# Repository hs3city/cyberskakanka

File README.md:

# cyberskakanka

## Wiring the Stuff Together

### Connecting Arduino and Weight Sensors

### Connecting Arduino and Raspberry Pi via I2C

### Connecting Raspberry Pi with WS212B LED Strip

## The Hardware

### The Base

### The Base with Two Tiles Fit

### The Tile

- 16mm MDF on the bottom
- a layer of white cardboard
- 5mm transparent plexi

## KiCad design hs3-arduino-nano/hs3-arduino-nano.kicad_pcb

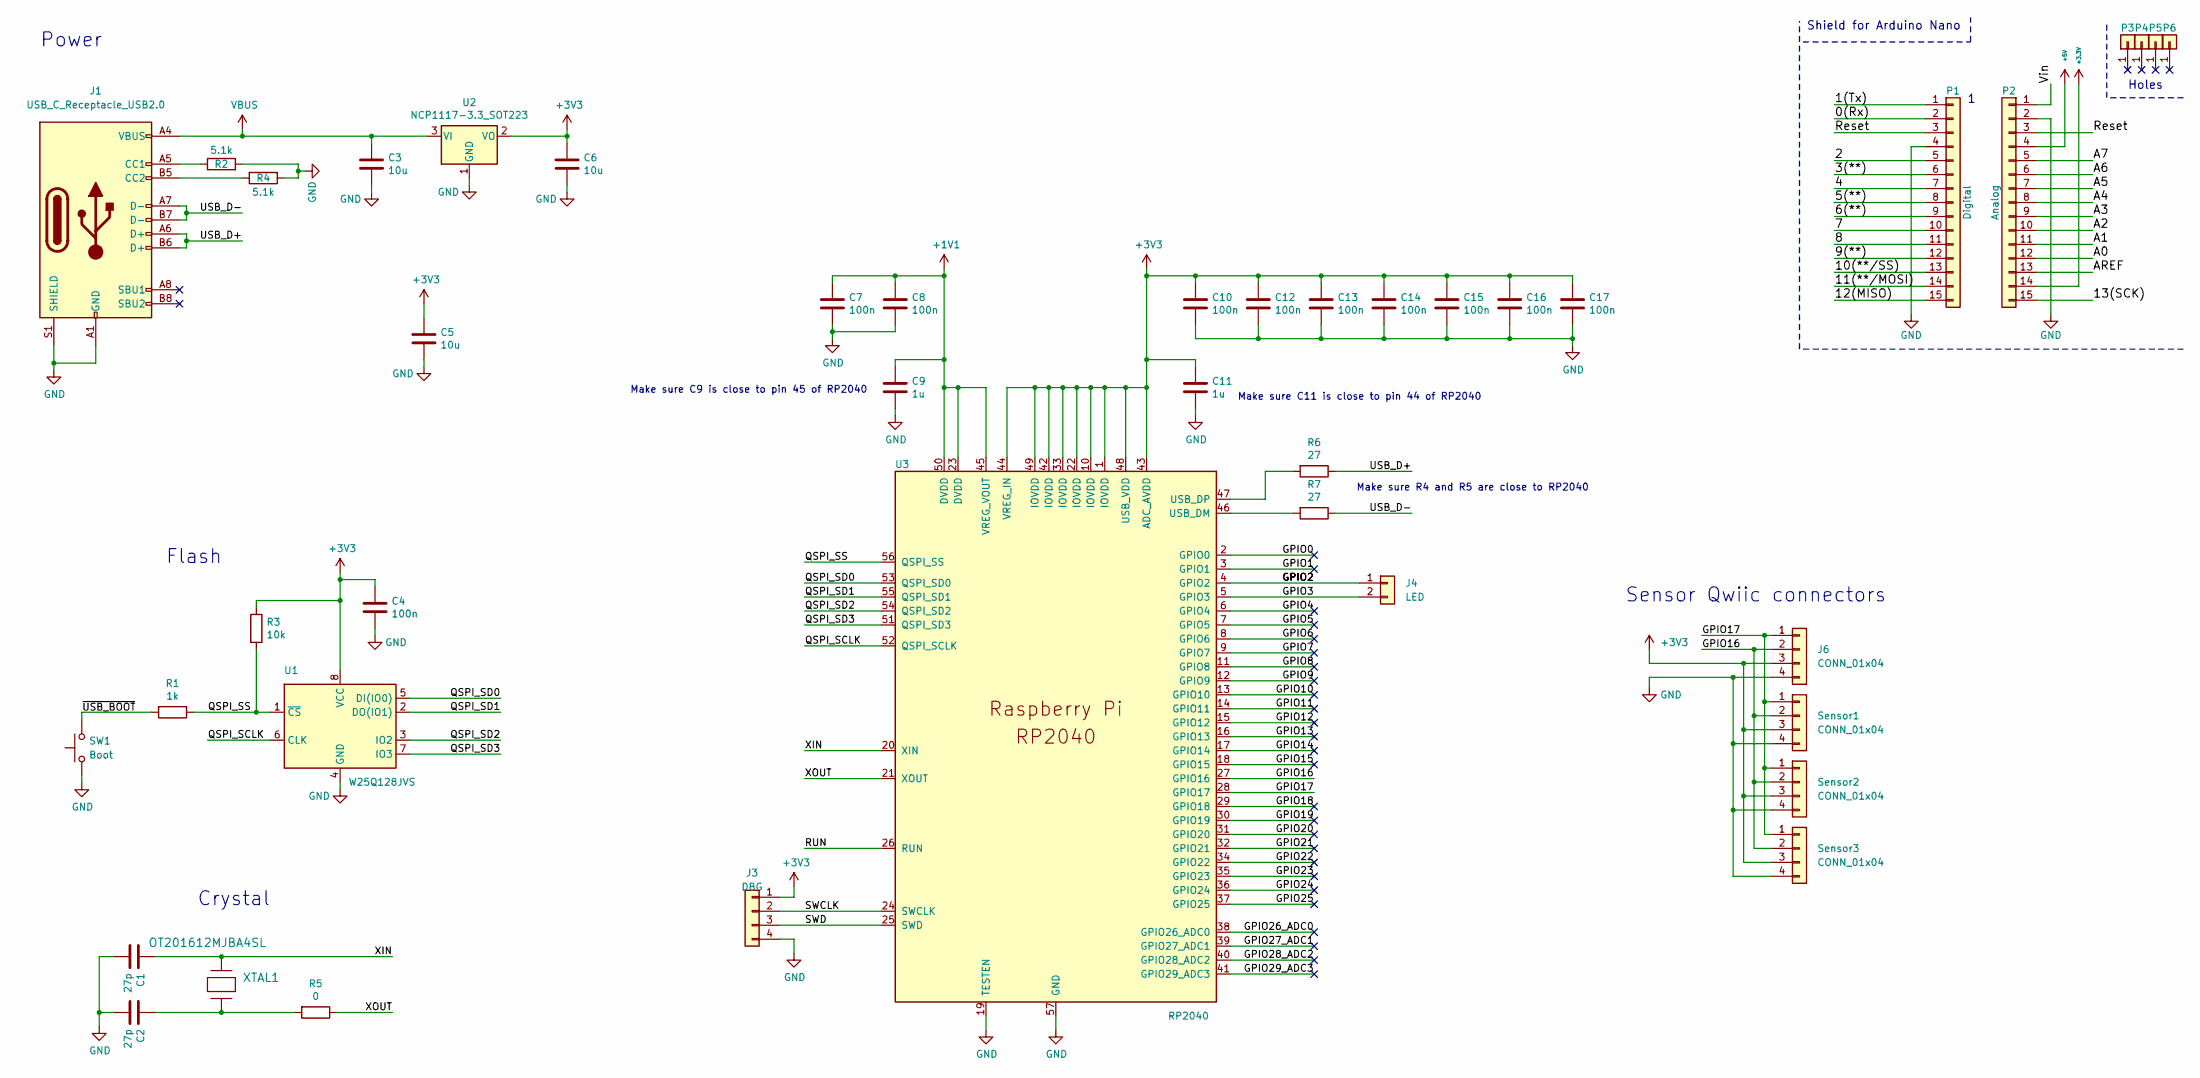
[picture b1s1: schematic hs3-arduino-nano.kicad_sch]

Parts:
C1, C2: 27p; C_0402_1005Metric; LCSC C1557
C3, C5, C6: 10u; C_0805_2012Metric; LCSC C15850
C4, C7, C8, C10, C12, C13, C14, C15, C16, C17: 100n; C_0402_1005Metric; LCSC C307331
C9, C11: 1u; C_0402_1005Metric; LCSC C52923
J1: USB_C_Receptacle_USB2.0; USB_C_Receptacle_HRO_TYPE-C-31-M-12
J3: DBG; PinHeader_1x04_P1.00mm_Vertical
J4: LED; PinHeader_1x02_P1.00mm_Vertical
J6: CONN_01x04; JST_SH_BM04B-SRSS-TB_1x04-1MP_P1.00mm_Vertical
P1: Digital; Socket_Strip_Arduino_1x15
P2: Analog; Socket_Strip_Arduino_1x15
P3, P4, P5, P6: CONN_01X01; 1pin_Nano
R1: 1k; R_0402_1005Metric; LCSC C25905
R2, R4: 5.1k; R_0402_1005Metric; LCSC C25905
R3: 10k; R_0402_1005Metric; LCSC C25744
R5: 0; R_0402_1005Metric; LCSC C17168
R6, R7: 27; R_0402_1005Metric; LCSC 0402
SW1: Boot; SW_SPST_CK_KXT3; LCSC C2689509
Sensor1, Sensor2, Sensor3: CONN_01x04; JST_SH_BM04B-SRSS-TB_1x04-1MP_P1.00mm_Vertical
U1: W25Q128JVS; SOIC-8_5.23x5.23mm_P1.27mm; LCSC C97521
U2: NCP1117-3.3_SOT223; SOT-223-3_TabPin2; LCSC C6186
U3: RP2040; RP2040-QFN-56; LCSC C2040
XTAL1: OT201612MJBA4SL; Crystal_SMD_2016-4Pin_2.0x1.6mm; LCSC C669076

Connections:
+1V1: C7.1, C8.1, C9.1, U3.23 (DVDD), U3.45 (VREG_VOUT), U3.50 (DVDD)
+3V3: C4.1, C5.1, C6.1, C10.1, C11.1, C12.1, C13.1, C14.1, C15.1, C16.1, C17.1, J3.1, J6.3, R3.1, Sensor1.3, Sensor2.3, Sensor3.3, U1.8 (VCC), U2.2 (VO), U3.1 (IOVDD), U3.10 (IOVDD), U3.22 (IOVDD), U3.33 (IOVDD), U3.42 (IOVDD), U3.43 (ADC_AVDD), U3.44 (VREG_IN), U3.48 (USB_VDD), U3.49 (IOVDD)
/GPIO0: U3.2 (GPIO0)
/GPIO1: U3.3 (GPIO1)
/GPIO3: J4.2, U3.5 (GPIO3)
/GPIO4: U3.6 (GPIO4)
/GPIO5: U3.7 (GPIO5)
/GPIO6: U3.8 (GPIO6)
/GPIO7: U3.9 (GPIO7)
/GPIO8: U3.11 (GPIO8)
/GPIO9: U3.12 (GPIO9)
/GPIO10: U3.13 (GPIO10)
/GPIO11: U3.14 (GPIO11)
/GPIO12: U3.15 (GPIO12)
/GPIO13: U3.16 (GPIO13)
/GPIO14: U3.17 (GPIO14)
/GPIO15: U3.18 (GPIO15)
/GPIO16: J6.2, Sensor1.2, Sensor2.2, Sensor3.2, U3.27 (GPIO16)
/GPIO17: J6.1, Sensor1.1, Sensor2.1, Sensor3.1, U3.28 (GPIO17)
/GPIO18: U3.29 (GPIO18)
/GPIO19: U3.30 (GPIO19)
/GPIO20: U3.31 (GPIO20)
/GPIO21: U3.32 (GPIO21)
/GPIO22: U3.34 (GPIO22)
/GPIO23: U3.35 (GPIO23)
/GPIO24: U3.36 (GPIO24)
/GPIO25: U3.37 (GPIO25)
/GPIO26_ADC0: U3.38 (GPIO26_ADC0)
/GPIO27_ADC1: U3.39 (GPIO27_ADC1)
/GPIO28_ADC2: U3.40 (GPIO28_ADC2)
/GPIO29_ADC3: U3.41 (GPIO29_ADC3)
/QSPI_SCLK: U1.6 (CLK), U3.52 (QSPI_SCLK)
/QSPI_SD0: U1.5 (DI(IO0)), U3.53 (QSPI_SD0)
/QSPI_SD1: U1.2 (DO(IO1)), U3.55 (QSPI_SD1)
/QSPI_SD2: U1.3 (IO2), U3.54 (QSPI_SD2)
/QSPI_SD3: U1.7 (IO3), U3.51 (QSPI_SD3)
/QSPI_SS: R1.1, R3.2, U1.1 (~CS), U3.56 (QSPI_SS)
/RUN: U3.26 (RUN)
/SWCLK: J3.2, U3.24 (SWCLK)
/SWD: J3.3, U3.25 (SWD)
/USB_D+: J1.A6 (D+), J1.B6 (D+), R6.1
/USB_D-: J1.A7 (D-), J1.B7 (D-), R7.1
/XIN: C1.1, U3.20 (XIN), XTAL1.3
/XOUT: R5.1, U3.21 (XOUT)
/~USB_BOOT: R1.2, SW1.2
GND: C1.2, C2.2, C3.2, C4.2, C5.2, C6.2, C7.2, C8.2, C9.2, C10.2, C11.2, C12.2, C13.2, C14.2, C15.2, C16.2, C17.2, J1.A1 (GND), J1.A12 (GND), J1.B1 (GND), J1.B12 (GND), J1.S1 (SHIELD), J3.4, J6.4, P1.4, P2.2, R2.2, R4.1, SW1.1, Sensor1.4, Sensor2.4, Sensor3.4, U1.4 (GND), U2.1 (GND), U3.19 (TESTEN), U3.57 (GND)
unnamed: C2.1, R5.2, XTAL1.1
unnamed: J1.A5 (CC1), R2.1
unnamed: J1.B5 (CC2), R4.2
unnamed: J4.1, U3.4 (GPIO2)
unnamed: P1.3, P2.3
unnamed: R6.2, U3.47 (USB_DP)
unnamed: R7.2, U3.46 (USB_DM)
VBUS: C3.1, J1.A4 (VBUS), J1.A9 (VBUS), J1.B4 (VBUS), J1.B9 (VBUS), U2.3 (VI)

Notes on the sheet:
Flash
Holes
Make sure C9 is close to pin 45 of RP2040
Shield for Arduino Nano
Make sure R4 and R5 are close to RP2040
Power
Make sure C11 is close to pin 44 of RP2040
Sensor Qwiic connectors
Crystal

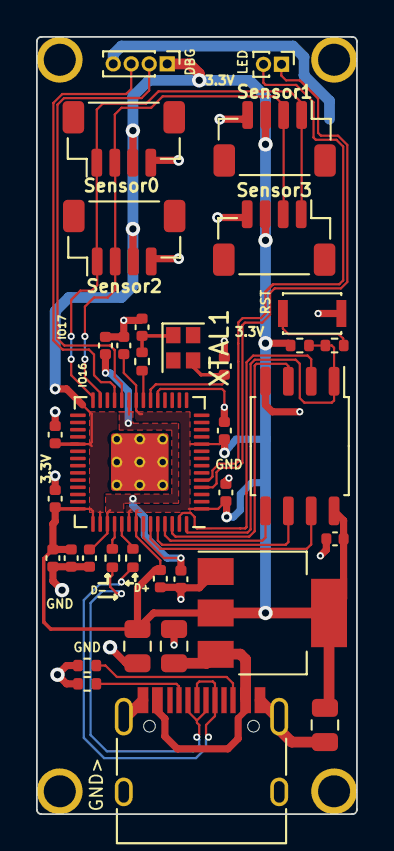
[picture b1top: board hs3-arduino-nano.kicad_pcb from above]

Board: 2 copper layers, 17.8 x 43.2 mm, 41 parts (0 on the bottom side), 26 nets.

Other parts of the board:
G2: LOGO

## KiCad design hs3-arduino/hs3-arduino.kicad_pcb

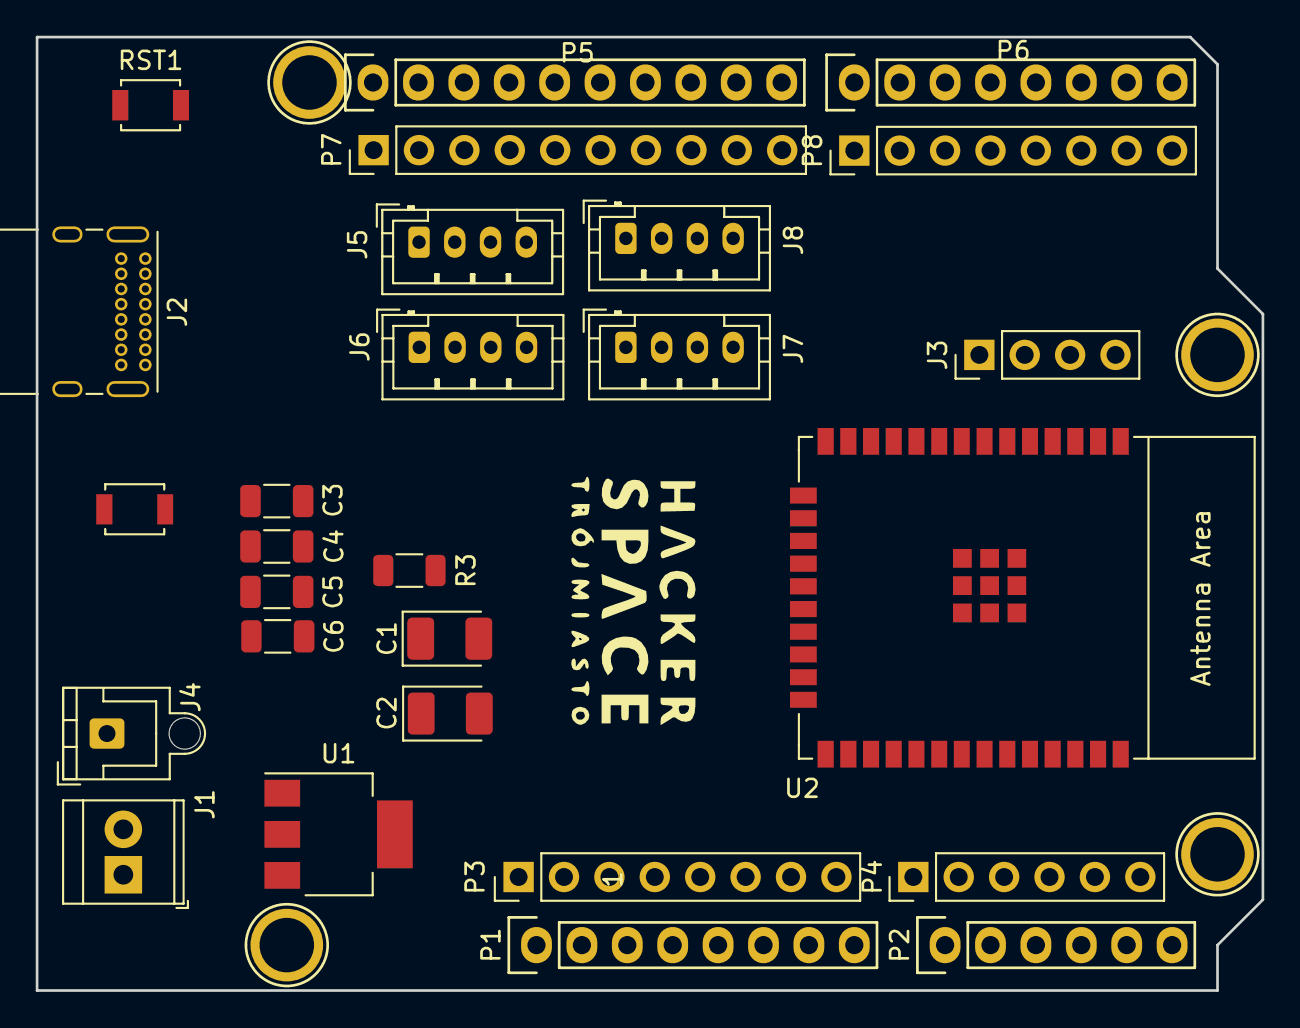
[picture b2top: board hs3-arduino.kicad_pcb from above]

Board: 2 copper layers, 68.6 x 53.3 mm, 31 parts (0 on the bottom side), 28 nets, no tracks yet.

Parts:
BOOT1: Boot Option; SW_SPST_B3U-1000P
C1, C2: 22uF; CP_EIA-3528-12_Kemet-T_Pad1.50x2.35mm_HandSolder
C3: 10u; C_1206_3216Metric
C4, C5, C6: 100nF; C_1206_3216Metric
J1: Conn_01x02; TerminalBlock_TE_282834-2_1x02_P2.54mm_Horizontal
J2: USB_C_Receptacle_USB2.0; USB_C_Receptacle_GCT_USB4085
J3: Serial; PinHeader_1x04_P2.54mm_Vertical
J4: LED Data; JST_XH_B1B-XH-AM_1x01_P2.50mm_Vertical
J5, J6, J7, J8: I2C Header; JST_PH_B4B-PH-K_1x04_P2.00mm_Vertical
P1: Power; Socket_Strip_Arduino_1x08
P2: Analog; Socket_Strip_Arduino_1x06
P3: Power; PinHeader_1x08_P2.54mm_Vertical
P4: Analog; PinHeader_1x06_P2.54mm_Vertical
P5: Digital; Socket_Strip_Arduino_1x10
P6: Digital; Socket_Strip_Arduino_1x08
P7: Digital; PinHeader_1x10_P2.54mm_Vertical
P8: Digital; PinHeader_1x08_P2.54mm_Vertical
P9, P10, P11, P12: CONN_01X01; Arduino_1pin
R3: 10k; R_1206_3216Metric
RST1: Reset; SW_SPST_B3U-1000P
U1: AMS1117-3.3; SOT-223-3_TabPin2
U2: ESP32-WROOM-32E

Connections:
+3V3: C2.1, C3.1, C4.1, J3.1, J5.1, J6.1, J7.1, J8.1, P1.4, P3.4, R3.1, U1.2 (VO), U2.2 (3V3)
+5V: C1.1, J1.1, P1.5, P1.8, P3.5, P3.8, U1.3 (VI)
/0(Rx): J3.3, P6.8, P8.8, U2.34 (U0RXD/GPIO3)
/1(Tx): J3.2, P6.7, P8.7, U2.35 (U0TXD/GPIO1)
/2: P6.6, P8.6, U2.24 (ADC2_CH2/GPIO2)
/3(**): P6.5, P8.5, U2.26 (ADC2_CH0/GPIO4)
/4: P6.4, P8.4, U2.29 (GPIO5)
/5(**): P6.3, P8.3, U2.27 (GPIO16)
/6(**): P6.2, P8.2, U2.28 (GPIO17)
/7: P6.1, P8.1, U2.30 (GPIO18)
/8: P5.10, P7.10, U2.31 (GPIO19)
/9(**): P5.9, P7.9, U2.33 (GPIO21)
/10(**/SS): P5.8, P7.8, U2.36 (GPIO22)
/11(**/MOSI): P5.7, P7.7, U2.37 (GPIO23)
/12(MISO): P5.6, P7.6, U2.10 (DAC_1/ADC2_CH8/GPIO25)
/13(SCK): P5.5, P7.5, U2.11 (DAC_2/ADC2_CH9/GPIO26)
/A0: P2.1, P4.1, U2.6 (GPIO34/ADC1_CH6)
/A1: P2.2, P4.2, U2.7 (GPIO35/ADC1_CH7)
/A2: P2.3, P4.3, U2.4 (SENSOR_VP/GPIO36/ADC1_CH0)
/A3: P2.4, P4.4, U2.5 (SENSOR_VN/GPIO39/ADC1_CH3)
/A4(SDA): J5.4, J6.4, J7.4, J8.4, P2.5, P4.5, P5.2, P7.2, U2.13 (MTMS/GPIO14/ADC2_CH6)
/A5(SCL): J5.3, J6.3, J7.3, J8.3, P2.6, P4.6, P5.1, P7.1, U2.23 (MTDO/GPIO15/ADC2_CH3)
/AREF: P5.3, P7.3
/Bootsel: BOOT1.2, U2.25 (GPIO0/BOOT/ADC2_CH1)
/IOREF: P1.2, P3.2
/LED Data: J4.1, U2.12 (ADC2_CH7/GPIO27)
/Reset: C5.1, C6.1, P1.3, R3.2, RST1.2, U2.3 (EN/CHIP_PU)
GND: BOOT1.1, C1.2, C2.2, C3.2, C4.2, C5.2, C6.2, J1.2, J3.4, J5.2, J6.2, J7.2, J8.2, P1.6, P1.7, P3.6, P3.7, P5.4, P7.4, RST1.1, U1.1 (GND), U2.1 (GND), U2.15 (GND), U2.38 (GND)

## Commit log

2022-03-25 EEPROM example
2022-04-01 Add some docs
2022-04-03 Add CAD renderings
2022-06-09 Adding duplicated Arduino pins
2022-06-13 Initial commit for Nano version of hs3-arduino
2022-06-13 Minor cleanup in element placement
2022-06-24 First stab at routing
2022-06-25 Redone placement, new routing
2022-06-26 Minor fixes to labels on silkscreen
2022-06-26 Post-review place & route update pt. 1
2022-06-27 Post-review place & route update pt. 2
2022-06-28 Adding KiCAD template to .gitignore
2022-06-28 Removing zip files from backups
2022-06-28 Removing backup files
2022-06-28 Shortening traces around 3.3V pins
2022-06-29 Minor cleanup in PCB, adding part numbers to BOM
2022-07-02 Adding manufacturing files
2022-07-14 Fixing footprint for xtal
2022-09-16 Fixing incorrect XTAL1 part number
